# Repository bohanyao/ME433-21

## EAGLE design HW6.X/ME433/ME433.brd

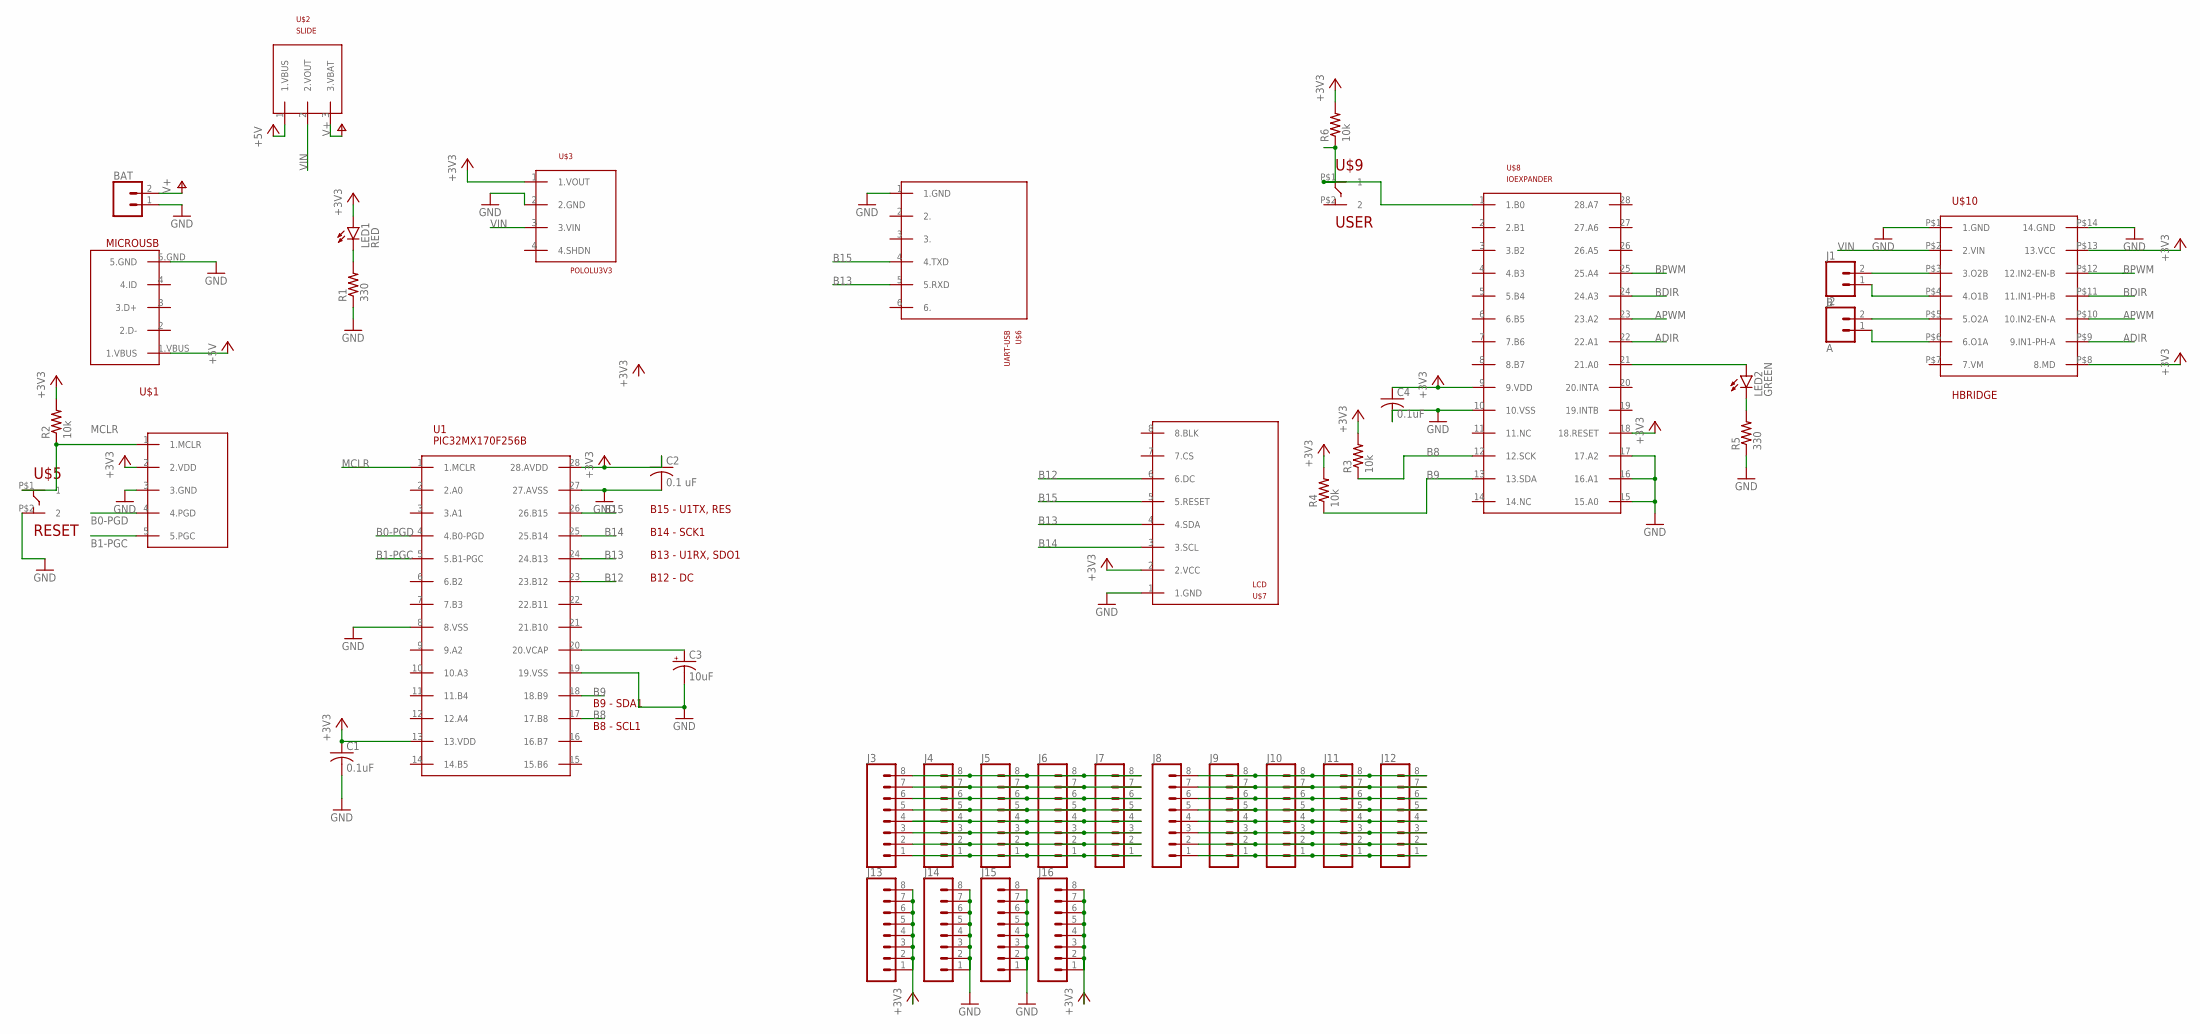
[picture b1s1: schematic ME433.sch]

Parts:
BAT: CONN_02; 1X02
C1, C4: 0.1uF; C025-030X050
C2: 0.1 uF; C025-030X050
C3: 10uF; B45181A
J1: B; 1X02
J2: A; 1X02
J3, J4, J5, J6, J7, J8, J9, J10, J11, J12, J13, J14, J15, J16: CONN_08"; 1X08
LED1: RED; LED3MM
LED2: GREEN; LED3MM
R1, R5: 330; 0207/10
R2, R3, R4, R6: 10k; 0207/10
U1: PIC32MX170F256B; DIL28-3
U$1: MICROUSB
U$2: SLIDE
U$3: POLOLU3V3
U$4: SNAP
U$5: RESET; PUSH
U$6: UART-USB
U$7: LCD
U$8: IOEXPANDER
U$9: USER; PUSH
U$10: HBRIDGE

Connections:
+3V3: C1.1, C2.1, C4.1, J13.1, J13.2, J13.3, J13.4, J13.5, J13.6, J13.7, J13.8, J16.1, J16.2, J16.3, J16.4, J16.5, J16.6, J16.7, J16.8, LED1.A, R2.2, R3.2, R4.2, R6.2, U1.13 (13.VDD), U1.28 (28.AVDD), U$3.1 (1.VOUT), U$4.2 (2.VDD), U$7.2 (2.VCC), U$8.9 (9.VDD), U$8.18 (18.RESET), U$10.P$8 (8.MD), U$10.P$13 (13.VCC)
+5V: U$1.1.VBUS, U$2.1 (1.VBUS)
ADIR: U$8.22 (22.A1), U$10.P$9 (9.IN1-PH-A)
APWM: U$8.23 (23.A2), U$10.P$10 (10.IN2-EN-A)
B0-PGD: U1.4 (4.B0-PGD), U$4.4 (4.PGD)
B1-PGC: U1.5 (5.B1-PGC), U$4.5 (5.PGC)
B8: R3.1, U1.17 (17.B8), U$8.12 (12.SCK)
B9: R4.1, U1.18 (18.B9), U$8.13 (13.SDA)
B12: U1.23 (23.B12), U$7.6 (6.DC)
B13: U1.24 (24.B13), U$6.5 (5.RXD), U$7.4 (4.SDA)
B14: U1.25 (25.B14), U$7.3 (3.SCL)
B15: U1.26 (26.B15), U$6.4 (4.TXD), U$7.5 (5.RESET)
BDIR: U$8.24 (24.A3), U$10.P$11 (11.IN1-PH-B)
BPWM: U$8.25 (25.A4), U$10.P$12 (12.IN2-EN-B)
GND: BAT.1, C1.2, C2.2, C3.-, C4.2, J14.1, J14.2, J14.3, J14.4, J14.5, J14.6, J14.7, J14.8, J15.1, J15.2, J15.3, J15.4, J15.5, J15.6, J15.7, J15.8, R1.1, R5.1, U1.8 (8.VSS), U1.19 (19.VSS), U1.27 (27.AVSS), U$1.5.GND, U$3.2 (2.GND), U$4.3 (3.GND), U$5.P$2 (2), U$6.1 (1.GND), U$7.1 (1.GND), U$8.10 (10.VSS), U$8.15 (15.A0), U$8.16 (16.A1), U$8.17 (17.A2), U$10.P$1 (1.GND), U$10.P$14 (14.GND)
MCLR: R2.1, U1.1 (1.MCLR), U$4.1 (1.MCLR), U$5.P$1 (1)
unnamed: LED1.K (C), R1.2
unnamed: J1.2, U$10.P$3 (3.O2B)
unnamed: C3.+, U1.20 (20.VCAP)
unnamed: J1.1, U$10.P$4 (4.O1B)
unnamed: LED2.A, U$8.21 (21.A0)
unnamed: LED2.K (C), R5.2
unnamed: J2.2, U$10.P$5 (5.O2A)
unnamed: J2.1, U$10.P$6 (6.O1A)
unnamed: J3.8, J4.8, J5.8, J6.8, J7.8
unnamed: J3.7, J4.7, J5.7, J6.7, J7.7
unnamed: J3.6, J4.6, J5.6, J6.6, J7.6
unnamed: J3.5, J4.5, J5.5, J6.5, J7.5
unnamed: J3.4, J4.4, J5.4, J6.4, J7.4
unnamed: J3.3, J4.3, J5.3, J6.3, J7.3
unnamed: J3.2, J4.2, J5.2, J6.2, J7.2
unnamed: J3.1, J4.1, J5.1, J6.1, J7.1
unnamed: J8.8, J9.8, J10.8, J11.8, J12.8
unnamed: J8.7, J9.7, J10.7, J11.7, J12.7
unnamed: J8.6, J9.6, J10.6, J11.6, J12.6
unnamed: J8.5, J9.5, J10.5, J11.5, J12.5
unnamed: J8.4, J9.4, J10.4, J11.4, J12.4
unnamed: J8.3, J9.3, J10.3, J11.3, J12.3
unnamed: J8.2, J9.2, J10.2, J11.2, J12.2
unnamed: J8.1, J9.1, J10.1, J11.1, J12.1
unnamed: R6.1, U$8.1 (1.B0), U$9.P$1 (1)
V+: BAT.2, U$2.3 (3.VBAT)
VIN: U$2.2 (2.VOUT), U$3.3 (3.VIN), U$10.P$2 (2.VIN)

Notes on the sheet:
B15 - U1TX, RES
B13 - U1RX, SDO1
B14 - SCK1
B12 - DC
B9 - SDA1
B8 - SCL1

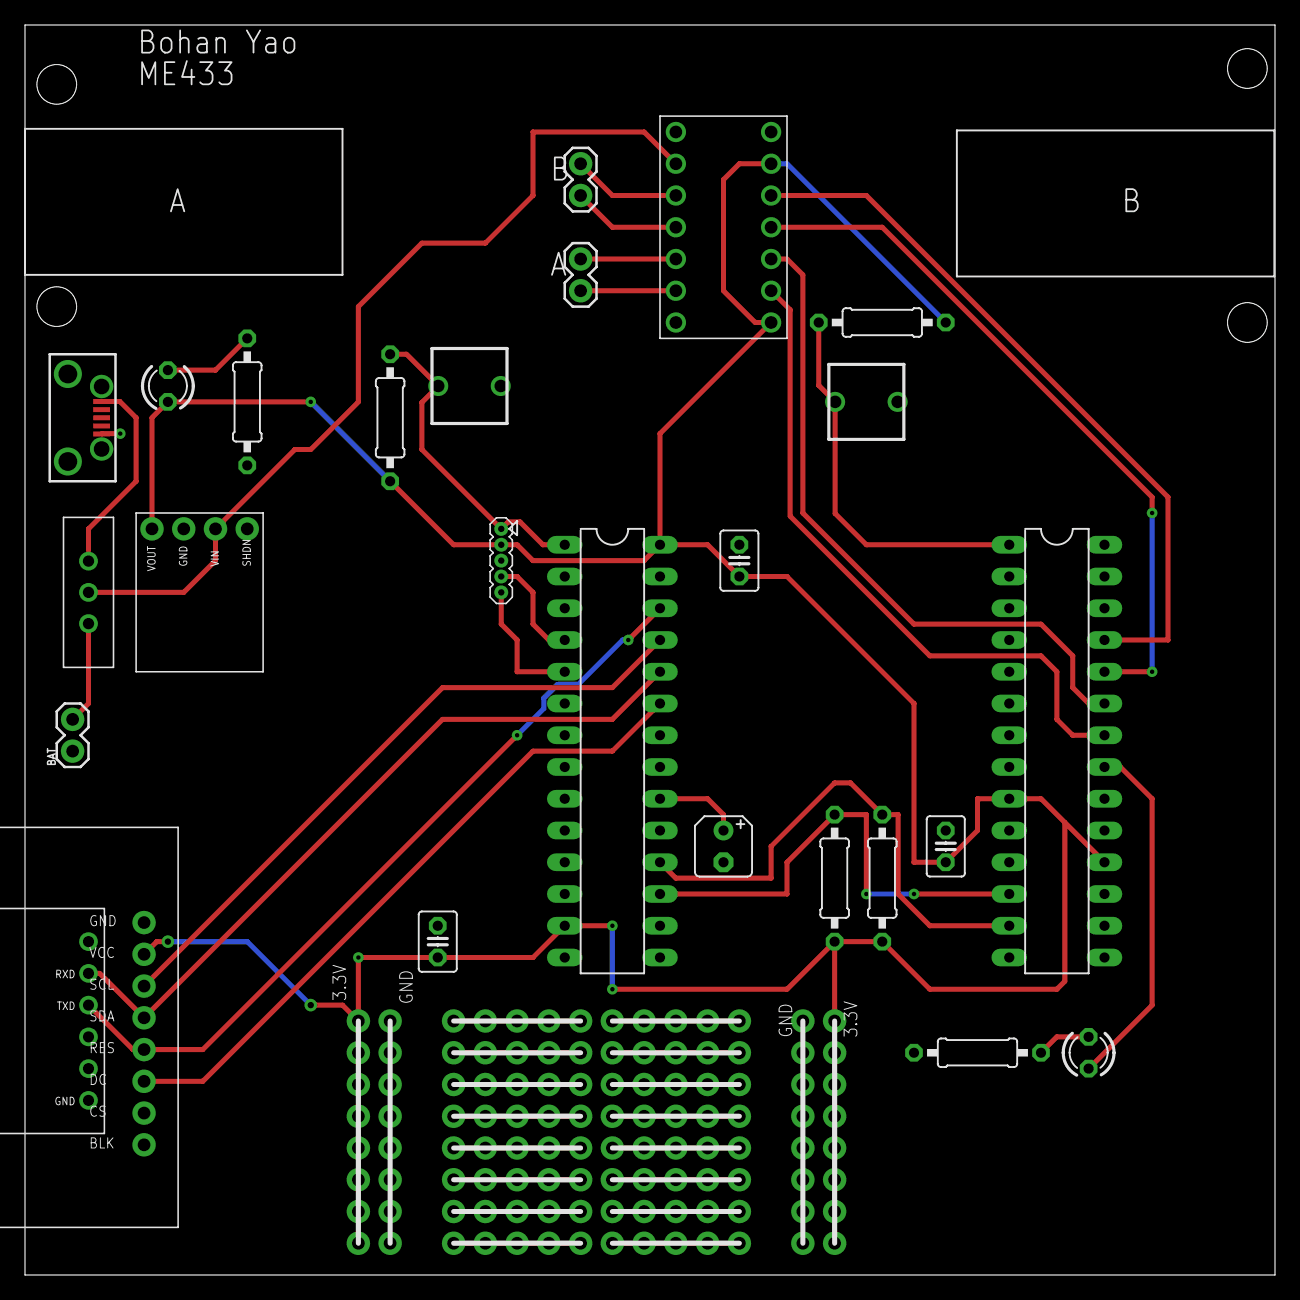
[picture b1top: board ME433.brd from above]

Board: 2 copper layers, 100.0 x 100.0 mm, 40 parts (0 on the bottom side), 43 nets.

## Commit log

2021-04-11 HW3 + 4
2021-04-23 HW7 + incomplete HW8
2021-04-28 HW6 (partial) + 8
2021-05-03 HW10
2021-05-10 HW9 + unfinished HW11
